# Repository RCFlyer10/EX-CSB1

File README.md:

# EX-CSB1
Open source EX-CSB1 CommandStation / Booster

Using the Bouni JLCPCB plugin to create the production files (gerbers) and handle all the parts subtitutions and rotations. Get the plugin from here:
https://github.com/Bouni/kicad-jlcpcb-tools

If your parts show up in the Kicad gerber viewer or in the JLC visual tool, import the corrections from our dcc-ex-rotation-corrections.csv file in the "support_files"folder.

 C:\Users\<user_name>\Documents\Kicad\<version>\3rdparty\plugins\com_github_bouni_kicad-jlcpcb-tools\jlcpcb
 
 Modified to include Booster Com connection that ties the DC power supply gnd between a command station and booster. I did this to eliminate any potiential problems.
 
 Removed the dual I2C headers from the board to make room for the new booster connection.
 
 Fixed the serial interface to be Arduino compliant.
 
 Added an option to provide vin power out by jumper (enabled by default).
 
 Added an option to provide ioref out by jumper (disabled by default).

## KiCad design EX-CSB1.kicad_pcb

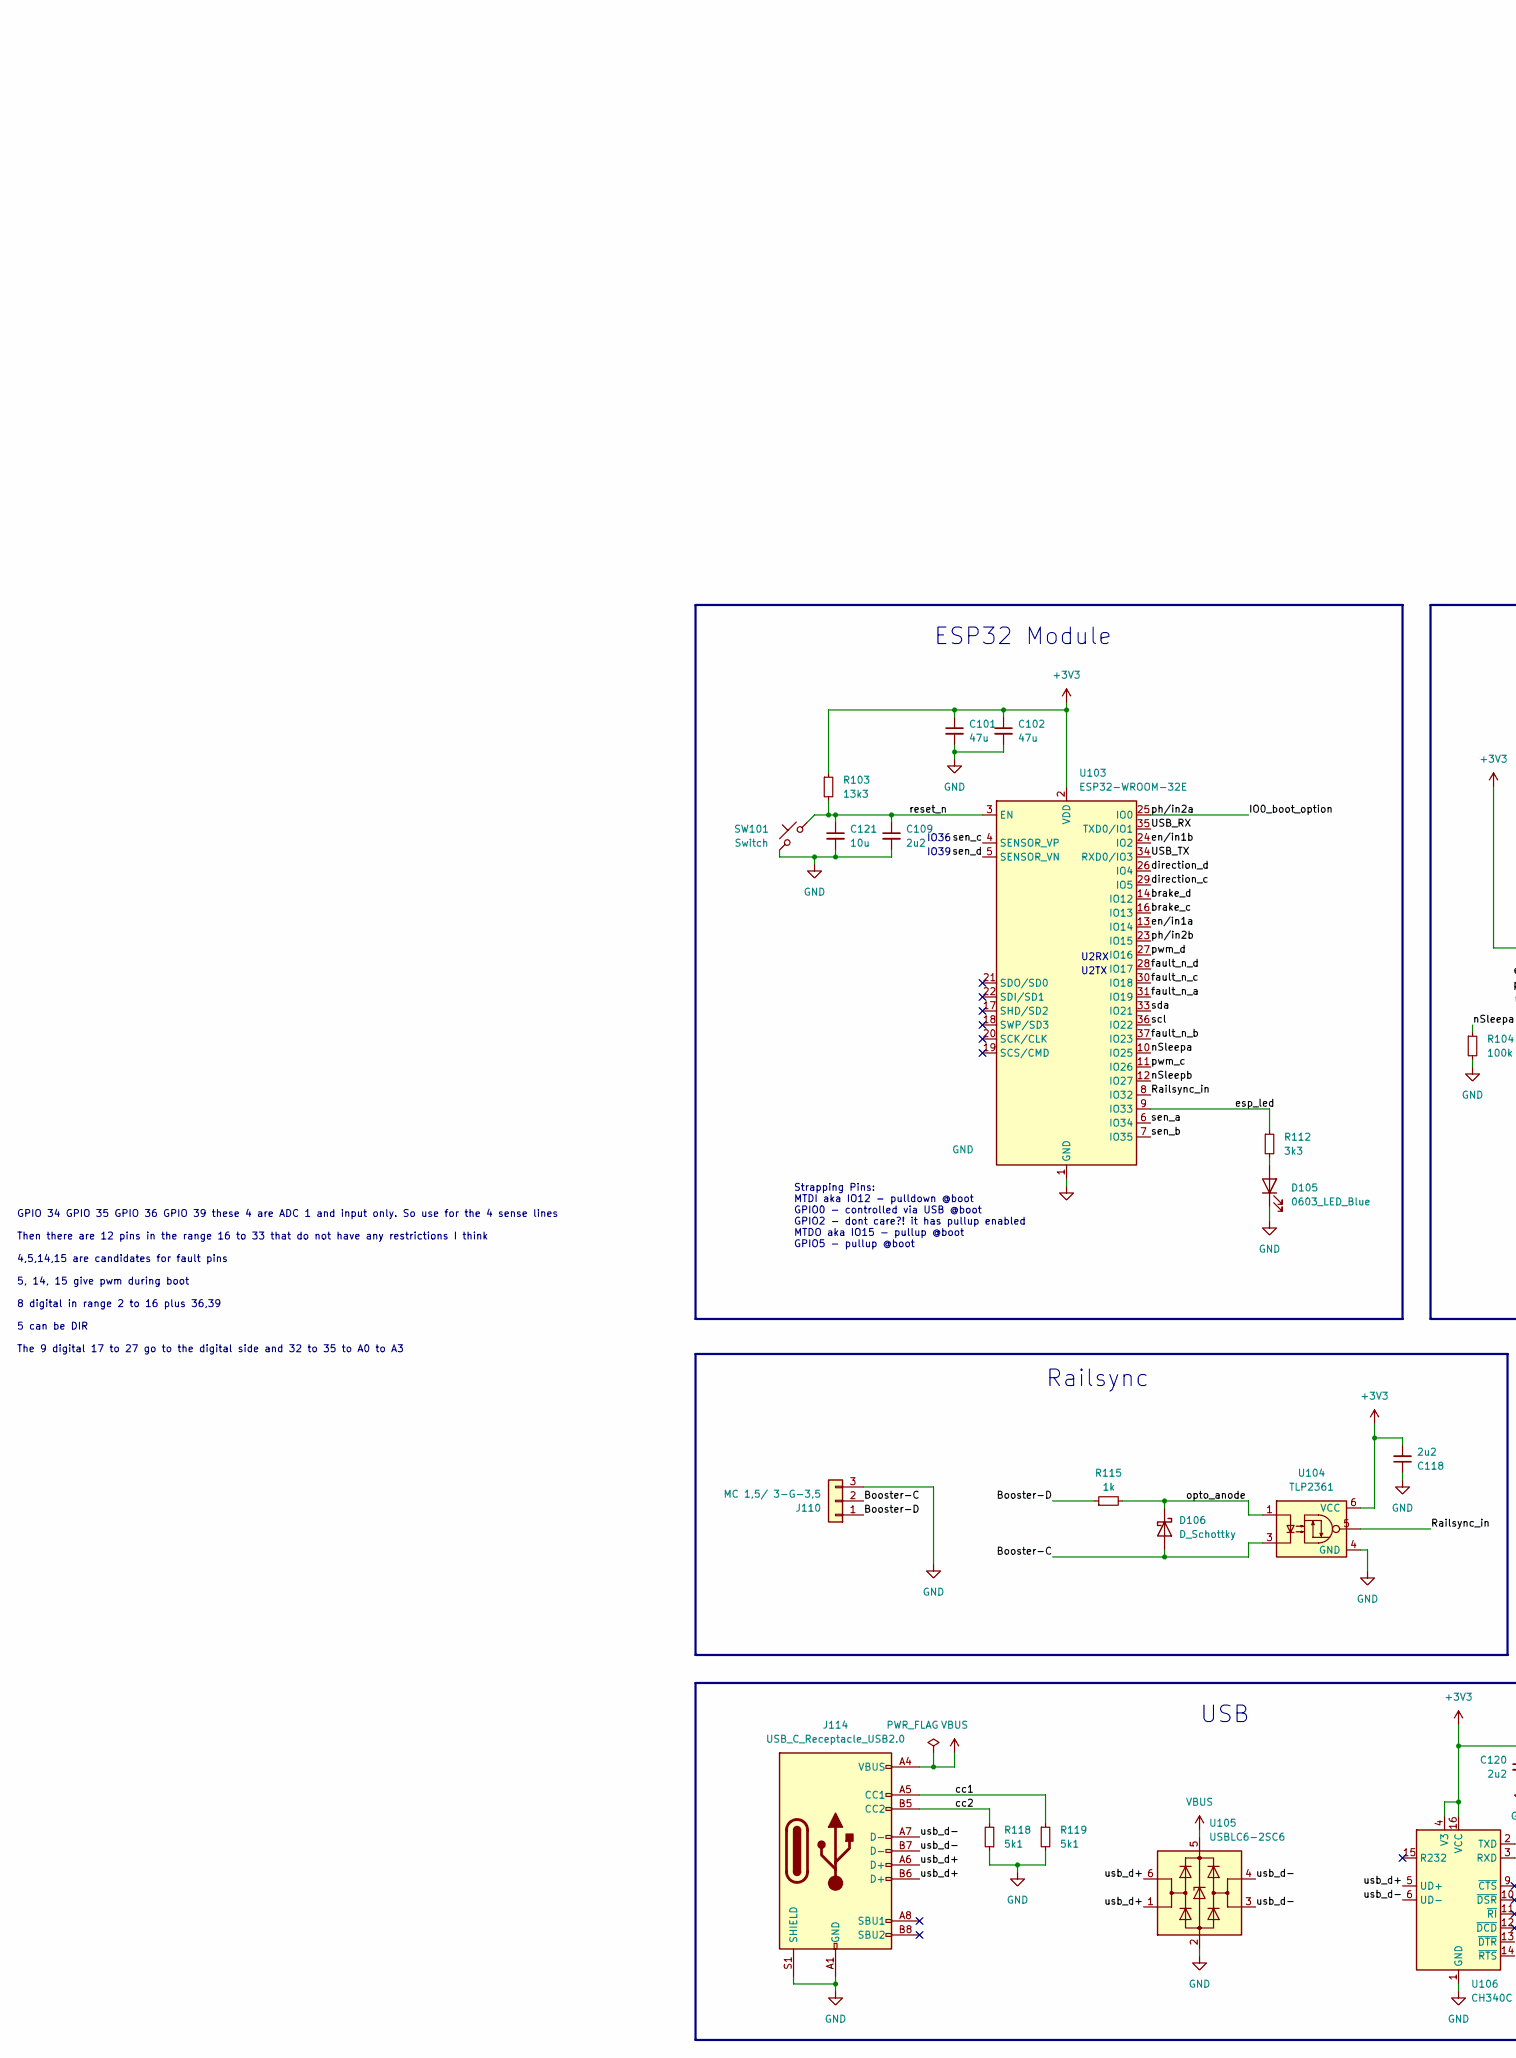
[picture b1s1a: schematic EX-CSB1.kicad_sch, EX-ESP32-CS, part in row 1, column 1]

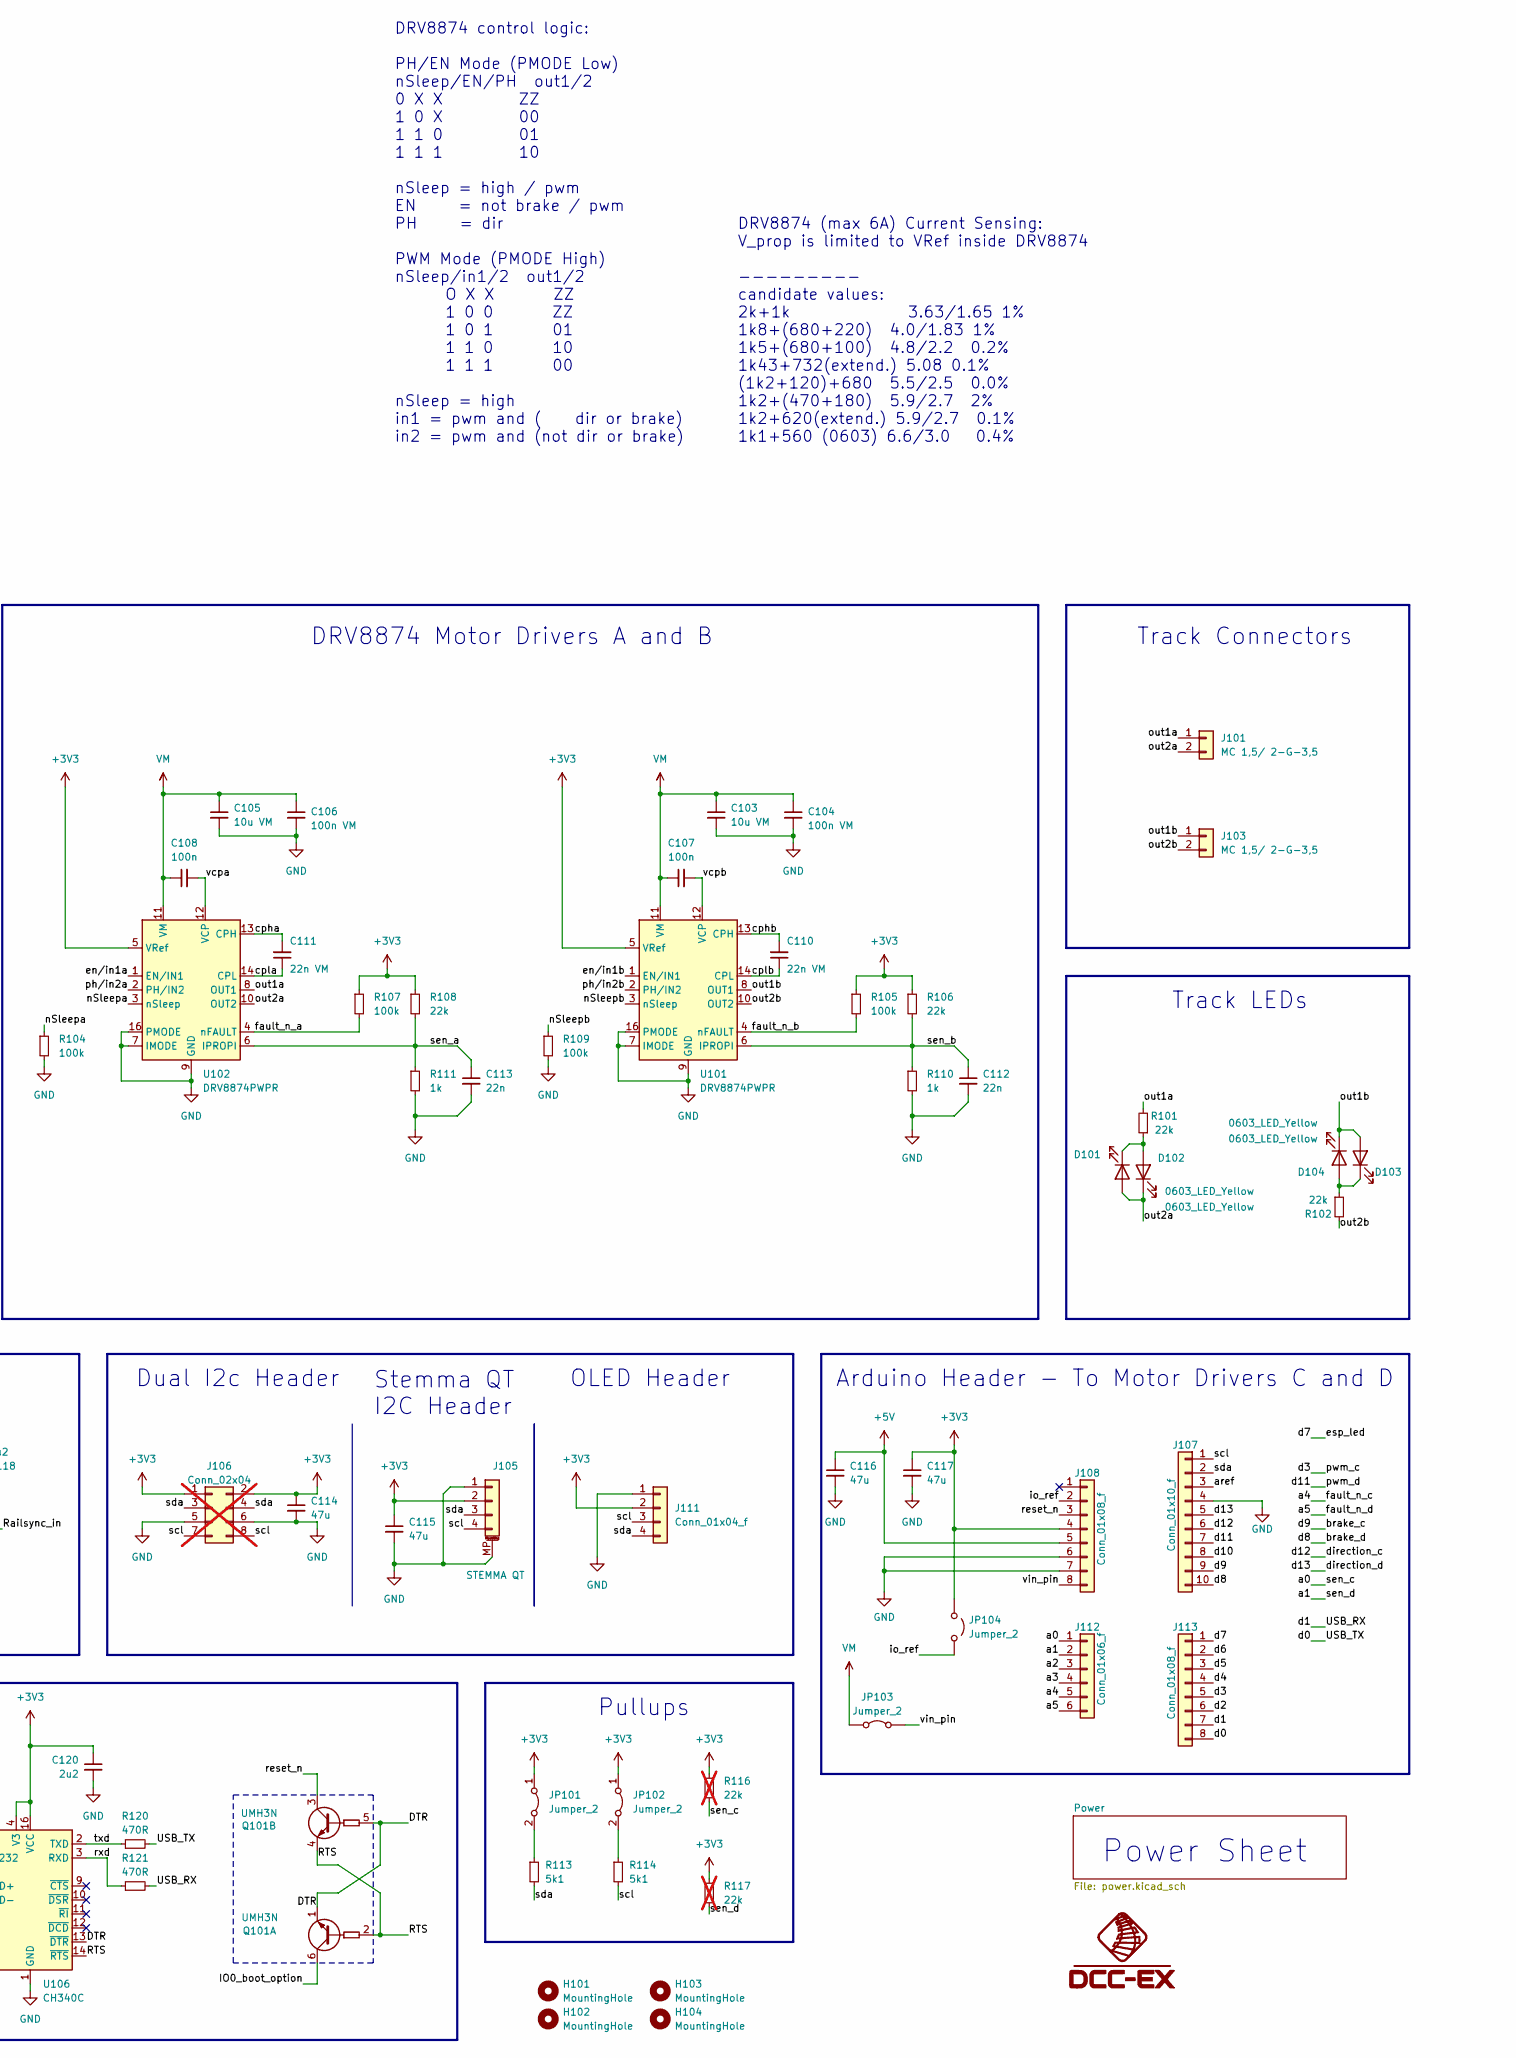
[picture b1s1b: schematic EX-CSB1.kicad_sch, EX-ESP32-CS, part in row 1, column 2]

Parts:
C101, C102, C114, C115, C116, C117: 47u; C_0805_2012Metric; LCSC Part # C16780
C103, C105: 10u VM; C_1206_3216Metric; LCSC Part # C13585
C104, C106: 100n VM; C_1005_(0402); LCSC Part # C307331
C107, C108: 100n; C_1005_(0402); LCSC Part # C1525
C109, C118, C120: 2u2; C_1005_(0402); LCSC Part # C12530
C110, C111: 22n VM; C_1005_(0402); LCSC Part # C337699
C112, C113: 22n; C_1005_(0402); LCSC Part # C337699
C121: 10u; C_0805_2012Metric
D101, D102, D103, D104: 0603_LED_Yellow; LED_0603_1608Metric; LCSC Part # C72038
D105: 0603_LED_Blue; LED_0603_1608Metric; LCSC Part # C965807
D106: D_Schottky; D_SMA; LCSC Part # C2480
H101, H102, H103, H104: MountingHole; MountingHole_2.2mm_M2_ISO7380_Pad
J101, J103: MC 1,5/ 2-G-3,5; PhoenixContact_MC_1,5_2-G-3.5_1x02_P3.50mm_Horizontal_edited; LCSC Part # C3581450
J105: STEMMA QT; JST_SH_SM04B-SRSS-TB_1x04-1MP_P1.00mm_Horizontal; LCSC Part # C160404
J106: Conn_02x04; PinHeader_2x04_P2.54mm_Vertical; LCSC Part # C492421; not fitted
J107: Conn_01x10_f; PinSocket_1x10_P2.54mm_Vertical; LCSC Part # C2935981
J108, J113: Conn_01x08_f; PinSocket_1x08_P2.54mm_Vertical; LCSC Part # C2935979
J110: MC 1,5/ 3-G-3,5; PhoenixContact_MC_1,5_3-G-3.5_1x03_P3.50mm_Horizontal
J111: Conn_01x04_f; PinSocket_1x04_P2.54mm_Vertical; LCSC Part # C2935898
J112: Conn_01x06_f; PinSocket_1x06_P2.54mm_Vertical; LCSC Part # C2935900
J114: USB_C_Receptacle_USB2.0; USB_C_Receptacle_GCT_USB4105-xx-A_16P_TopMnt_Horizontal; LCSC Part # C2765186
JP101, JP102: Jumper_2; SolderJumper-2_P1.3mm_Bridged
JP103: Jumper_2; SolderJumper-2_P1.3mm_Bridged_RoundedPad1.0x1.5mm
JP104: Jumper_2; SolderJumper-2_P1.3mm_Open_RoundedPad1.0x1.5mm
Q101: UMH3N; SOT-363_SC-70-6; LCSC Part # C62892
R101, R102, R106, R108: 22k; R_1005_(0402); LCSC Part # C137898
R103: 13k3; R_1005_(0402); LCSC Part # C274352
R104, R105, R107, R109: 100k; R_1005_(0402); LCSC Part # C60491
R110, R111, R115: 1k; R_1005_(0402); LCSC Part # C106235
R112: 3k3; R_1005_(0402); LCSC Part # C137992
R113, R114, R118, R119: 5k1; R_1005_(0402); LCSC Part # C105872
R116, R117: 22k; R_1005_(0402); LCSC Part # C137898; not fitted
R120, R121: 470R; R_1005_(0402); LCSC Part # C114877
SW101: Switch; SW_SPST_TS-1088-AR02016; LCSC Part # C720477
U101, U102: DRV8874PWPR; HTSSOP-16-1EP_4.4x5mm_P0.65mm_EP3.4x5mm_Mask2.46_HiAmp; LCSC Part # C1855818
U103: ESP32-WROOM-32E; LCSC Part # C701341
U104: TLP2361; SO-5_4.4x3.6mm_P1.27mm; LCSC Part # C107626
U105: USBLC6-2SC6; SOT-23-6; LCSC Part # C2687116
U106: CH340C; SOIC-16_3.9x9.9mm_P1.27mm; LCSC Part # C7464026

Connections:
+3V3: C101.1, C102.1, C114.1, C115.1, C117.1, C118.2, C120.1, J105.2, J106.1, J106.2, J108.4, J111.2, JP101.1 (A), JP102.1 (A), JP104.1 (A), R103.1, R105.1, R106.1, R107.1, R108.1, R116.1, R117.1, U101.5 (VRef), U102.5 (VRef), U103.2 (VDD), U104.6 (VCC), U106.4 (V3), U106.16 (VCC); also elsewhere on the board
+5V: C116.1, J108.5; also elsewhere on the board
/Booster-C: D106.2 (A), J110.2, U104.3
/Booster-D: J110.1, R115.1
/DTR: Q101.1 (E1), Q101.5 (B2), U106.13 (~DTR)
/IO0_boot_option: Q101.6 (C1), U102.2 (PH/IN2), U103.25 (IO0)
/RTS: Q101.2 (B1), Q101.4 (E2), U106.14 (~RTS)
/Railsync_in: U103.8 (IO32), U104.5
/USB_RX: J113.7, R121.2, U103.35 (TXD0/IO1)
/USB_TX: J113.8, R120.2, U103.34 (RXD0/IO3)
/a0: J112.1, R116.2, U103.4 (SENSOR_VP)
/a1: J112.2, R117.2, U103.5 (SENSOR_VN)
/a2: J112.3
/a3: J112.4
/a4: J112.5, U103.30 (IO18)
/a5: J112.6, U103.28 (IO17)
/aref: J107.3
/brake_c: J107.9, U103.16 (IO13)
/brake_d: J107.10, U103.14 (IO12)
/cc1: J114.A5 (CC1), R119.1
/cc2: J114.B5 (CC2), R118.2
/cpha: C111.2, U102.13 (CPH)
/cphb: C110.2, U101.13 (CPH)
/cpla: C111.1, U102.14 (CPL)
/cplb: C110.1, U101.14 (CPL)
/d2: J113.6
/d3: J113.5, U103.11 (IO26)
/d4: J113.4
/d5: J113.3
/d6: J113.2
/d7: J113.1, R112.1, U103.9 (IO33)
/d10: J107.8
/d11: J107.7, U103.27 (IO16)
/d12: J107.6, U103.29 (IO5)
/d13: J107.5, U103.26 (IO4)
/en/in1a: U102.1 (EN/IN1), U103.13 (IO14)
/en/in1b: U101.1 (EN/IN1), U103.24 (IO2)
/fault_n_a: R107.2, U102.4 (nFAULT), U103.31 (IO19)
/fault_n_b: R105.2, U101.4 (nFAULT), U103.37 (IO23)
/io_ref: J108.2, JP104.2 (B)
/nSleepa: R104.1, U102.3 (nSleep), U103.10 (IO25)
/nSleepb: R109.1, U101.3 (nSleep), U103.12 (IO27)
/opto_anode: D106.1 (K), R115.2, U104.1
/out1a: J101.1, R101.2, U102.8 (OUT1)
/out1b: D103.2 (A), D104.1 (K), J103.1, U101.8 (OUT1)
/out2a: D101.2 (A), D102.1 (K), J101.2, U102.10 (OUT2)
/out2b: J103.2, R102.2, U101.10 (OUT2)
/ph/in2b: U101.2 (PH/IN2), U103.23 (IO15)
/reset_n: C109.1, C121.1, J108.3, Q101.3 (C2), R103.2, SW101.1, U103.3 (EN)
/rxd: R121.1, U106.3 (RXD)
/scl: J105.4, J106.7, J106.8, J107.1, J111.3, R114.2, U103.36 (IO22)
/sda: J105.3, J106.3, J106.4, J107.2, J111.4, R113.2, U103.33 (IO21)
/sen_a: C113.1, R108.2, R111.1, U102.6 (IPROPI), U103.6 (IO34)
/sen_b: C112.1, R106.2, R110.1, U101.6 (IPROPI), U103.7 (IO35)
/txd: R120.1, U106.2 (TXD)
/usb_d+: J114.A6 (D+), J114.B6 (D+), U105.1 (I/O1), U105.6 (I/O1), U106.5 (UD+)
/usb_d-: J114.A7 (D-), J114.B7 (D-), U105.3 (I/O2), U105.4 (I/O2), U106.6 (UD-)
/vcpa: C108.2, U102.12 (VCP)
/vcpb: C107.2, U101.12 (VCP)
/vin_pin: J108.8, JP103.2 (B)
GND: C101.2, C102.2, C103.2, C104.2, C105.2, C106.2, C109.2, C112.2, C113.2, C114.2, C115.2, C116.2, C117.2, C118.1, C120.2, C121.2, D105.1 (K), J105.1, J105.MP (MountPin), J106.5, J106.6, J107.4, J108.6, J108.7, J110.3, J111.1, J114.A1 (GND), J114.A12 (GND), J114.B1 (GND), J114.B12 (GND), J114.S1 (SHIELD), R104.2, R109.2, R110.2, R111.2, R118.1, R119.2, SW101.2, U101.7 (IMODE), U101.9 (GND), U101.15 (GND), U101.16 (PMODE), U101.17 (GND), U102.7 (IMODE), U102.9 (GND), U102.15 (GND), U102.16 (PMODE), U102.17 (GND), U103.1 (GND), U103.15 (GND), U103.38 (GND), U103.39 (GND), U104.4 (GND), U105.2 (GND), U106.1 (GND); also elsewhere on the board
unnamed: D101.1 (K), D102.2 (A), R101.1
unnamed: D103.1 (K), D104.2 (A), R102.1
unnamed: D105.2 (A), R112.2
unnamed: JP101.2 (B), R113.1
unnamed: JP102.2 (B), R114.1
VBUS: J114.A4 (VBUS), J114.A9 (VBUS), J114.B4 (VBUS), J114.B9 (VBUS), U105.5 (VBUS); also elsewhere on the board
VM: C103.1, C104.1, C105.1, C106.1, C107.1, C108.1, JP103.1 (A), U101.11 (VM), U102.11 (VM); also elsewhere on the board

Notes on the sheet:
Power Sheet
Railsync
USB
Pullups
Strapping Pins: MTDI aka IO12 - pulldown @boot GPIO0 - controlled via USB @boot GPIO2 - dont care?! it has pullup enabled MTDO aka IO15 - pullup @boot GPIO5 - pullup @boot
Track LEDs
GPIO 34 GPIO 35 GPIO 36 GPIO 39 these 4 are ADC 1 and input only. So use for the 4 sense lines Then there are 12 pins in the range 16 to 33 that do not have any restrictions I think 4,5,14,15 are candidates for fault pins 5, 14, 15 give pwm during boot 8 digital in range 2 to 16 plus 36,39 5 can be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
U2RX
DRV8874 Motor Drivers A and B
IO36
DRV8874 (max 6A) Current Sensing: V_prop is limited to VRef inside DRV8874 --------- candidate values: 2k+1k 3.63/1.65 1% 1k8+(680+220) 4.0/1.83 1% 1k5+(680+100) 4.8/2.2 0.2% 1k43+732(extend.) 5.08 0.1% (1k2+120)+680 5.5/2.5 0.0% 1k2+(470+180) 5.9/2.7 2% 1k2+620(extend.) 5.9/2.7 0.1% 1k1+560 (0603)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
U2TX
DRV8874 control logic: PH/EN Mode (PMODE Low) nSleep/EN/PH out1/2 0 X X ZZ 1 0 X 00 1 1 0 01 1 1 1 10 nSleep = high / pwm EN = not brake / pwm PH = dir PWM Mode (PMODE High) nSleep/in1/2 out1/2 O X X ZZ 1 0 0 ZZ 1 0 1 01 1 1 0 10 1 1 1 00 nSleep = high in1 = pwm and ( dir or brake) in2 = pwm and (n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
Arduino Header - To Motor Drivers C and D
Track Connectors
IO39
OLED Header
Stemma QT I2C Header
Dual I2c Header
ESP32 Module

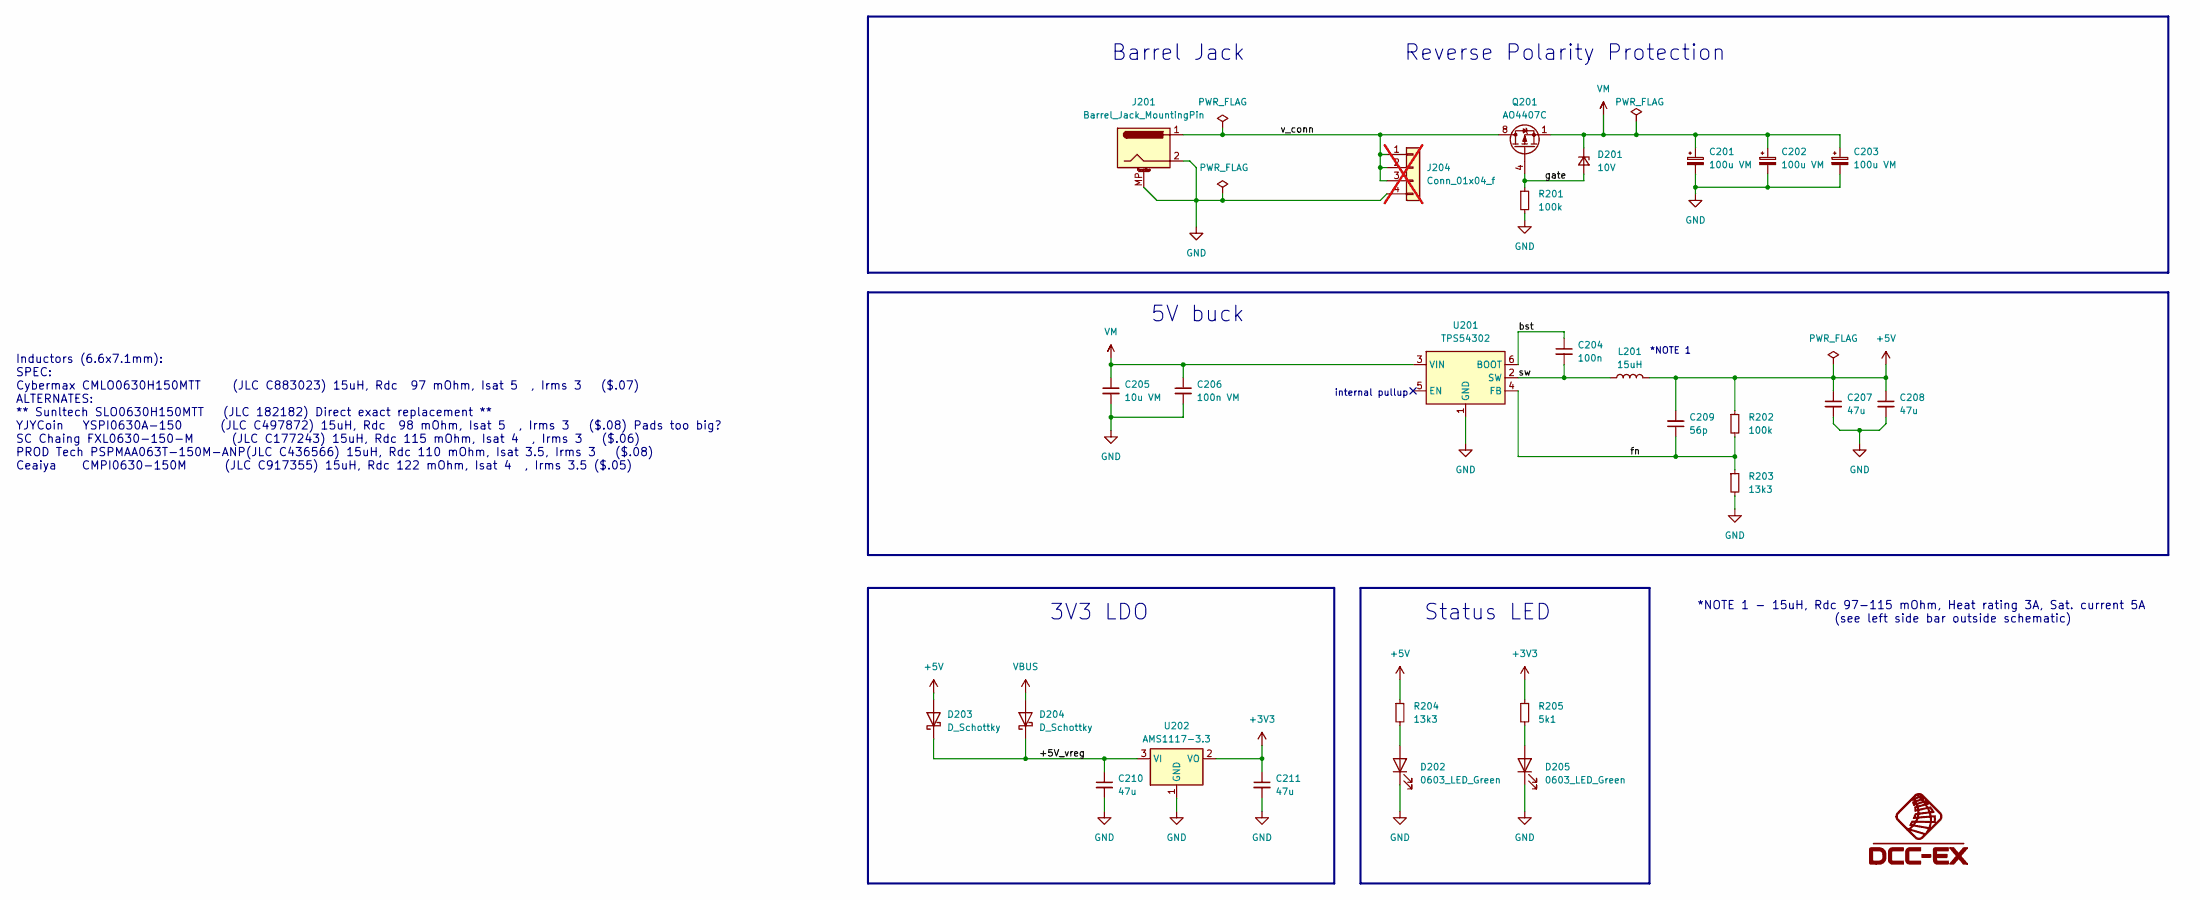
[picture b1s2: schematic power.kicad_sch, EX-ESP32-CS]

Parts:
C201, C202, C203: 100u VM; CP_Elec_6.3x7.7; LCSC Part # C2972719
C204: 100n; C_1005_(0402); LCSC Part # C1525
C205: 10u VM; C_1206_3216Metric; LCSC Part # C13585
C206: 100n VM; C_1005_(0402); LCSC Part # C307331
C207, C208, C210, C211: 47u; C_0805_2012Metric; LCSC Part # C16780
C209: 56p; C_1005_(0402); LCSC Part # C107007
D201: 10V; D_SOD-323; LCSC Part # C85383
D202, D205: 0603_LED_Green; LED_0603_1608Metric; LCSC Part # C965804
D203, D204: D_Schottky; D_SMA; LCSC Part # C2480
J201: Barrel_Jack_MountingPin; BarrelJack_2.1mm; LCSC Part # C381116
J204: Conn_01x04_f; PinSocket_1x04_P2.54mm_Vertical; LCSC Part # C2685089; not fitted
L201: 15uH; L_7.1x6.6_H3_SLO0630H; LCSC Part # C883023
Q201: AO4407C; SOIC-8_3.9x4.9mm_P1.27mm; LCSC Part # C469397
R201, R202: 100k; R_1005_(0402); LCSC Part # C60491
R203, R204: 13k3; R_1005_(0402); LCSC Part # C274352
R205: 5k1; R_1005_(0402); LCSC Part # C105872
U201: TPS54302; SOT-23-6; LCSC Part # C311983
U202: AMS1117-3.3; SOT-223-3_TabPin2; LCSC Part # C6186

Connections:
+3V3: C211.1, R205.1, U202.2 (VO); also elsewhere on the board
+5V: C207.1, C208.1, C209.2, D203.2 (A), L201.2, R202.1, R204.1; also elsewhere on the board
/Power/+5V_vreg: C210.1, D203.1 (K), D204.1 (K), U202.3 (VI)
/Power/bst: C204.1, U201.6 (BOOT)
/Power/fn: C209.1, R202.2, R203.1, U201.4 (FB)
/Power/gate: D201.2 (A), Q201.4 (G), R201.1
/Power/sw: C204.2, L201.1, U201.2 (SW)
/Power/v_conn: J201.1, J204.1, J204.2, J204.3, Q201.5 (D), Q201.6 (D), Q201.7 (D), Q201.8 (D)
GND: C201.2, C202.2, C203.2, C205.2, C206.2, C207.2, C208.2, C210.2, C211.2, D202.1 (K), D205.1 (K), J201.2, J201.MP (MountPin), J204.4, R201.2, R203.2, U201.1 (GND), U202.1 (GND); also elsewhere on the board
unnamed: D202.2 (A), R204.2
unnamed: D205.2 (A), R205.2
VBUS: D204.2 (A); also elsewhere on the board
VM: C201.1, C202.1, C203.1, C205.1, C206.1, D201.1 (K), Q201.1 (S), Q201.2 (S), Q201.3 (S), U201.3 (VIN); also elsewhere on the board

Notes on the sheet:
Inductors (6.6x7.1mm): SPEC: Cybermax CMLO0630H150MTT (JLC C883023) 15uH, Rdc 97 mOhm, Isat 5 , Irms 3 ($.07) ALTERNATES: ** Sunltech SLO0630H150MTT (JLC 182182) Direct exact replacement ** YJYCoin YSPI0630A-150 (JLC C497872) 15uH, Rdc 98 mOhm, Isat 5 , Irms 3 ($.08) Pads too big? SC Chaing FXL0630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
Status LED
3V3 LDO
internal pullup
Reverse Polarity Protection
*NOTE 1 - 15uH, Rdc 97-115 mOhm, Heat rating 3A, Sat. current 5A (see left side bar outside schematic)
*NOTE 1
5V buck
Barrel Jack

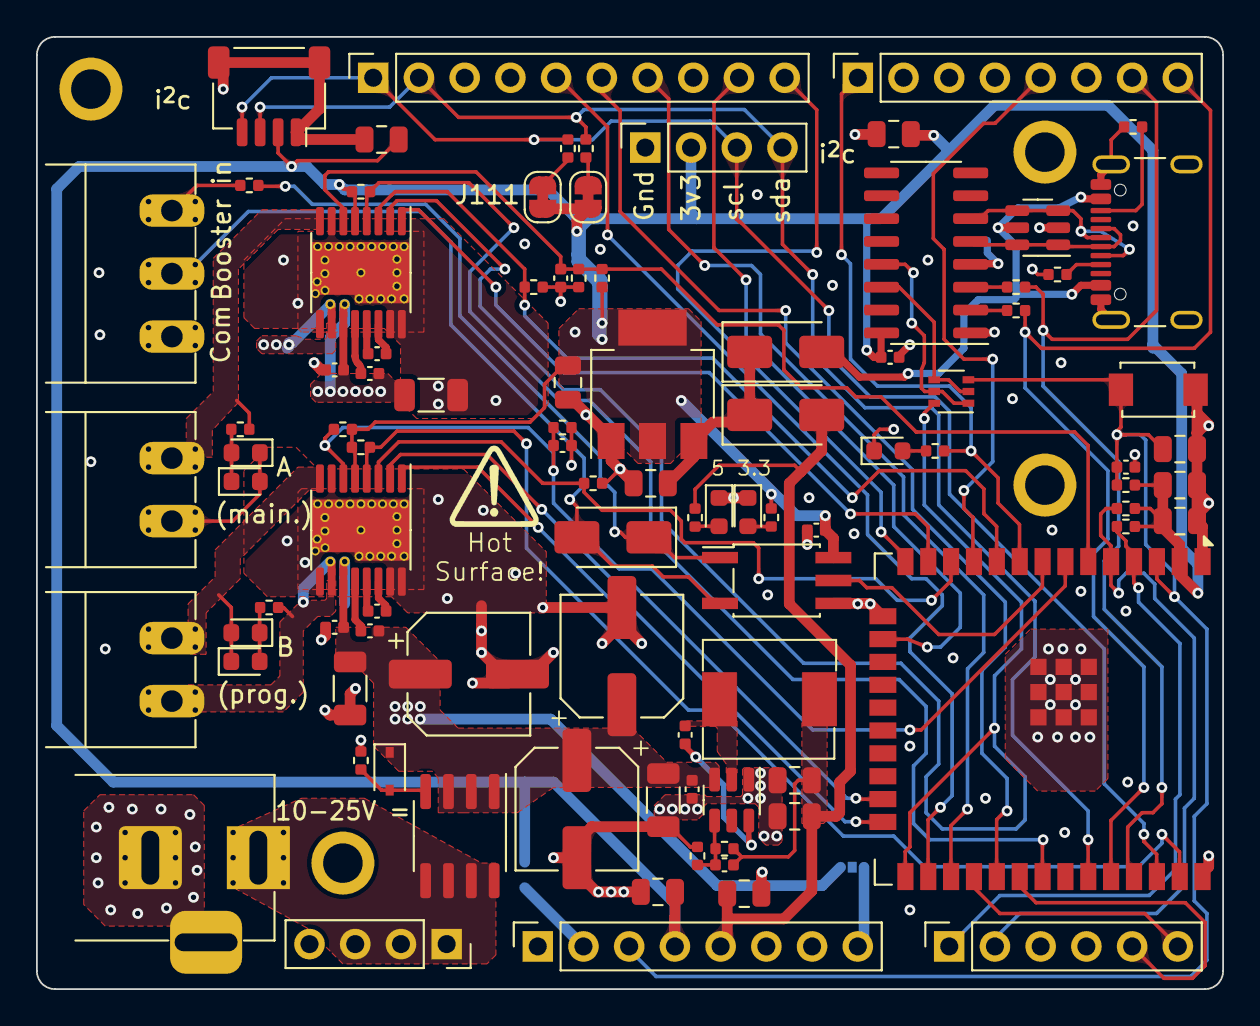
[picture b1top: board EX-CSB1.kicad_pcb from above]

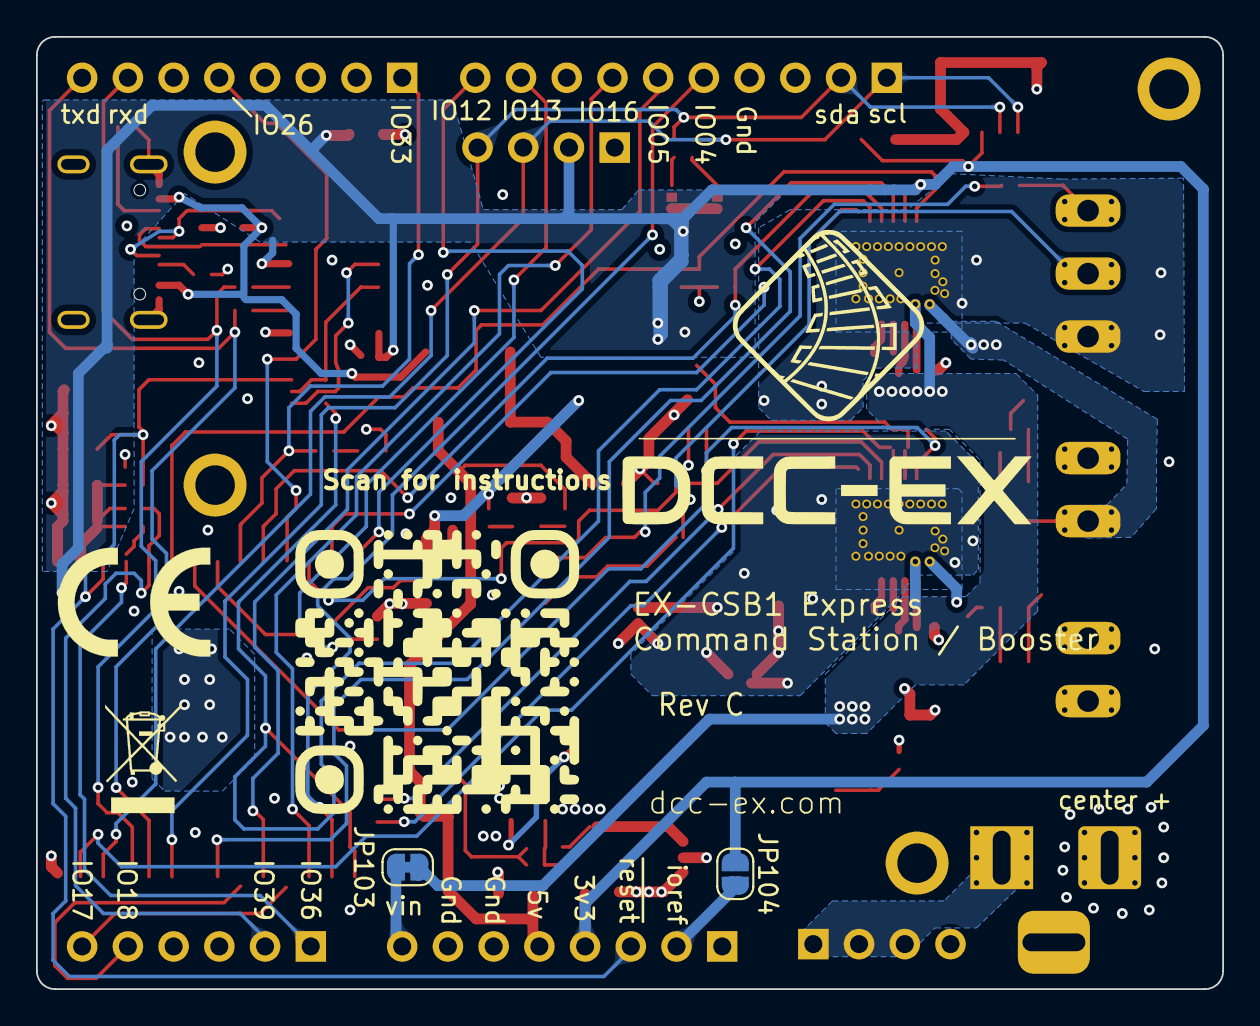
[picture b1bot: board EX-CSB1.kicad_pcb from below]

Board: 4 copper layers, 65.9 x 52.9 mm, 100 parts (2 on the bottom side), 68 nets.

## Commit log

2025-05-22 Rev C
    Removed dual I2C header to make room, Added booter common, fixed serial to conform with arduino standard, added option to provide vin_pin out by jumper (enabled by default) and added option to provid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

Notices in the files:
EX-CSB1.kicad_sch:
CERN-OHL-W v2 or later
Licensed under
